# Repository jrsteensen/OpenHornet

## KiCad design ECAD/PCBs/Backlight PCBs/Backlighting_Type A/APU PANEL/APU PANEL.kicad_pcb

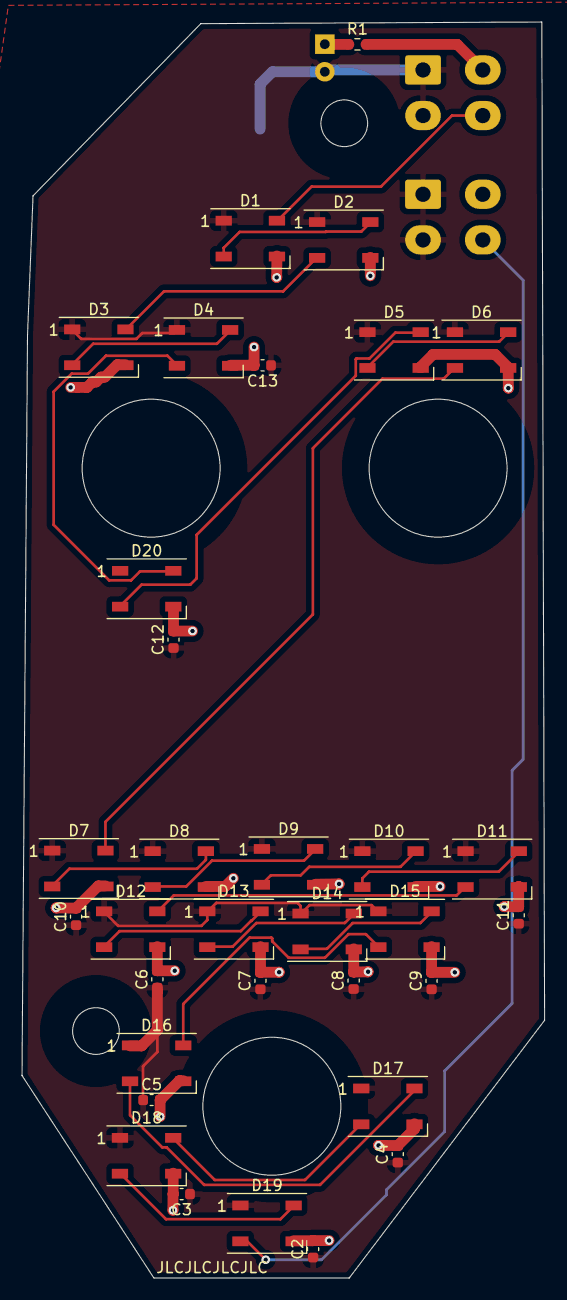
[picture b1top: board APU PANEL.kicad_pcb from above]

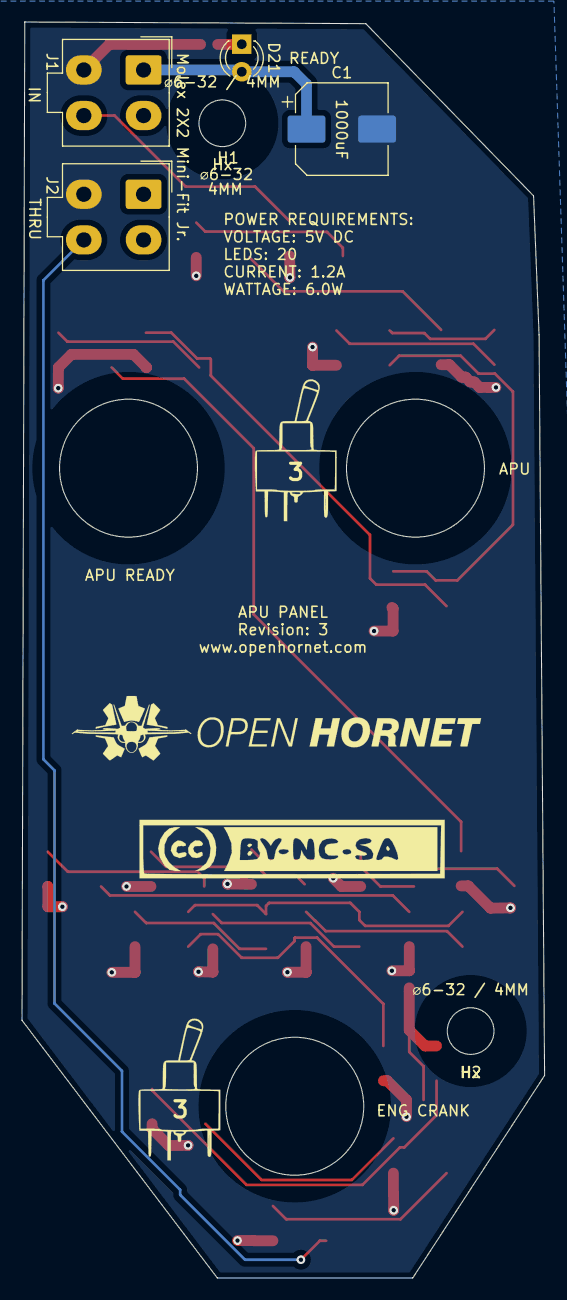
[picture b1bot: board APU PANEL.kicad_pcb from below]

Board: 2 copper layers, 48.1 x 115.6 mm, 41 parts (4 on the bottom side), 24 nets.

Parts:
2, 3: 631H_Toggle_13mm_x_13mm
4, 5: OH_Panel_Fastner_Keepout; OH_Panel_6-32_PHS
C1: 1000uF (C_Polarized); CP_Elec_8x10
C2, C3, C4, C5, C6, C7, C8, C9, C10, C11, C12, C13: 0.1uF; C_0603_1608Metric
D1, D2, D3, D4, D5, D6, D7, D8, D9, D10, D11, D12, D13, D14, D15, D16, D17, D18, D19, D20: WS2812B; LED_WS2812B_PLCC4_5.0x5.0mm_P3.2mm
D21: LED; LED_D3.0mm
J1, J2: 2x02; Molex_Mini-Fit_Jr_5566-04A_2x02_P4.20mm_Vertical
R1: 470; R_0603_1608Metric

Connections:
/DATAIN: D1.4 (DIN), J1.4
/DATAOUT: D19.2 (DOUT), J2.4
/LED+5V: C1.1, C2.1, C3.1, C4.1, C5.1, C6.1, C7.1, C8.1, C9.1, C10.1, C11.1, C12.1, C13.1, D1.1 (VDD), D2.1 (VDD), D3.1 (VDD), D4.1 (VDD), D5.1 (VDD), D6.1 (VDD), D7.1 (VDD), D8.1 (VDD), D9.1 (VDD), D10.1 (VDD), D11.1 (VDD), D12.1 (VDD), D13.1 (VDD), D14.1 (VDD), D15.1 (VDD), D16.1 (VDD), D17.1 (VDD), D18.1 (VDD), D19.1 (VDD), D20.1 (VDD), D21.2 (A), J1.1, J1.2, J2.1, J2.2
/LEDGND: C1.2, C2.2, C3.2, C4.2, C5.2, C6.2, C7.2, C8.2, C9.2, C10.2, C11.2, C12.2, C13.2, D1.3 (VSS), D2.3 (VSS), D3.3 (VSS), D4.3 (VSS), D5.3 (VSS), D6.3 (VSS), D7.3 (VSS), D8.3 (VSS), D9.3 (VSS), D10.3 (VSS), D11.3 (VSS), D12.3 (VSS), D13.3 (VSS), D14.3 (VSS), D15.3 (VSS), D16.3 (VSS), D17.3 (VSS), D18.3 (VSS), D19.3 (VSS), D20.3 (VSS), J1.3, J2.3, R1.2
unnamed: D1.2 (DOUT), D2.4 (DIN)
unnamed: D2.2 (DOUT), D3.4 (DIN)
unnamed: D3.2 (DOUT), D4.4 (DIN)
unnamed: D5.2 (DOUT), D6.4 (DIN)
unnamed: D6.2 (DOUT), D7.4 (DIN)
unnamed: D7.2 (DOUT), D8.4 (DIN)
unnamed: D8.2 (DOUT), D9.4 (DIN)
unnamed: D10.2 (DOUT), D11.4 (DIN)
unnamed: D9.2 (DOUT), D10.4 (DIN)
unnamed: D11.2 (DOUT), D12.4 (DIN)
unnamed: D12.2 (DOUT), D13.4 (DIN)
unnamed: D13.2 (DOUT), D14.4 (DIN)
unnamed: D14.2 (DOUT), D15.4 (DIN)
unnamed: D15.2 (DOUT), D16.4 (DIN)
unnamed: D16.2 (DOUT), D17.4 (DIN)
unnamed: D17.2 (DOUT), D18.4 (DIN)
unnamed: D18.2 (DOUT), D19.4 (DIN)
unnamed: D5.4 (DIN), D20.2 (DOUT)
unnamed: D4.2 (DOUT), D20.4 (DIN)
unnamed: D21.1 (K), R1.1

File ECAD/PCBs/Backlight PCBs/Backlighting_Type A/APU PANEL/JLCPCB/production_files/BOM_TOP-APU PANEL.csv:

Comment,Designator,Footprint,LCSC
0.1uF,"C10,C11,C12,C13,C2,C3,C4,C5,C6,C7,C8,C9",C_0603_1608Metric,C14663
470,R1,R_0603_1608Metric,C23179
WS2812B,"D1,D10,D11,D12,D13,D14,D15,D16,D17,D18,D19,D2,D20,D3,D4,D5,D6,D7,D8,D9",LED_WS2812B_PLCC4_5.0x5.0mm_P3.2mm,C2761795

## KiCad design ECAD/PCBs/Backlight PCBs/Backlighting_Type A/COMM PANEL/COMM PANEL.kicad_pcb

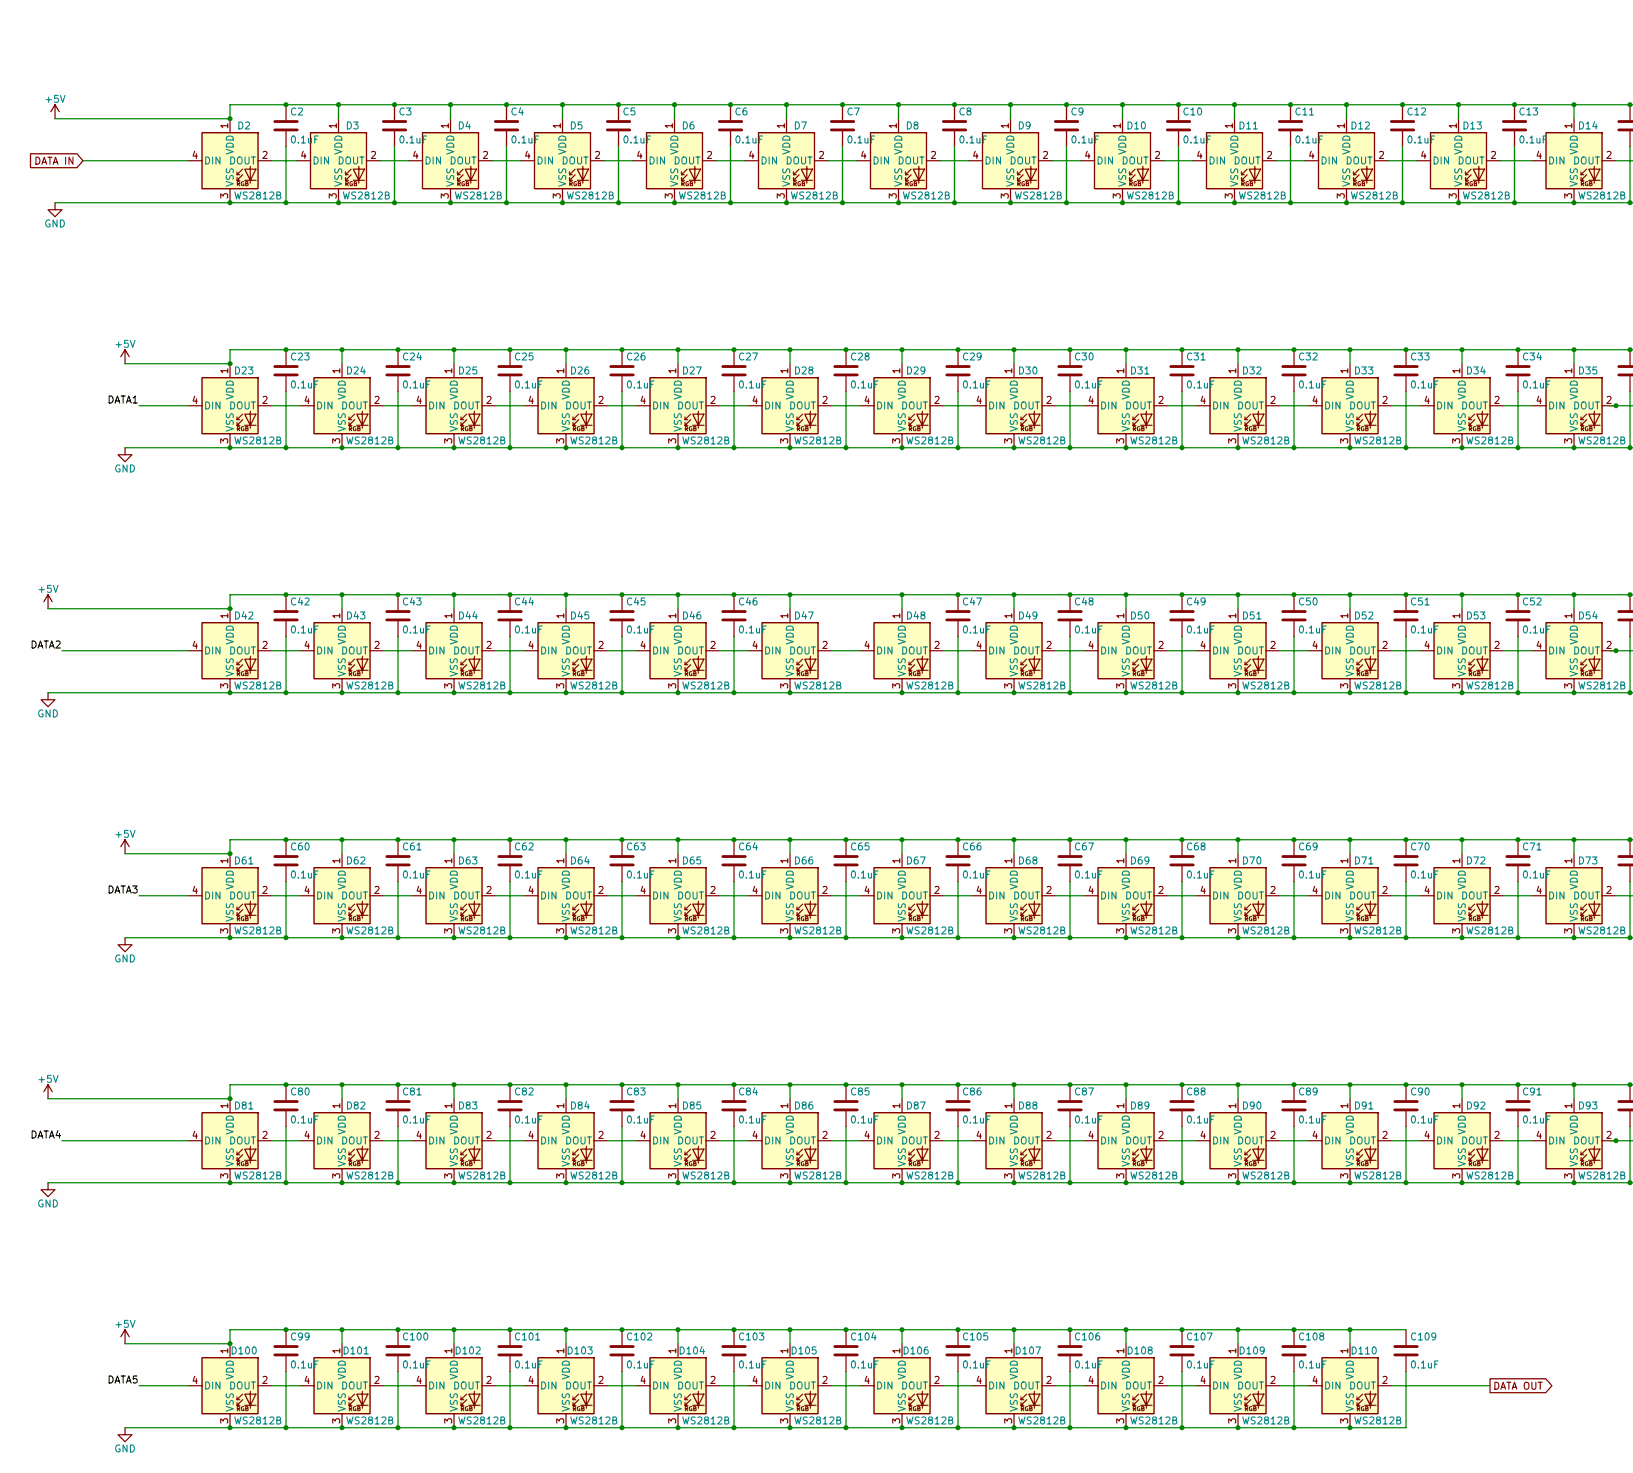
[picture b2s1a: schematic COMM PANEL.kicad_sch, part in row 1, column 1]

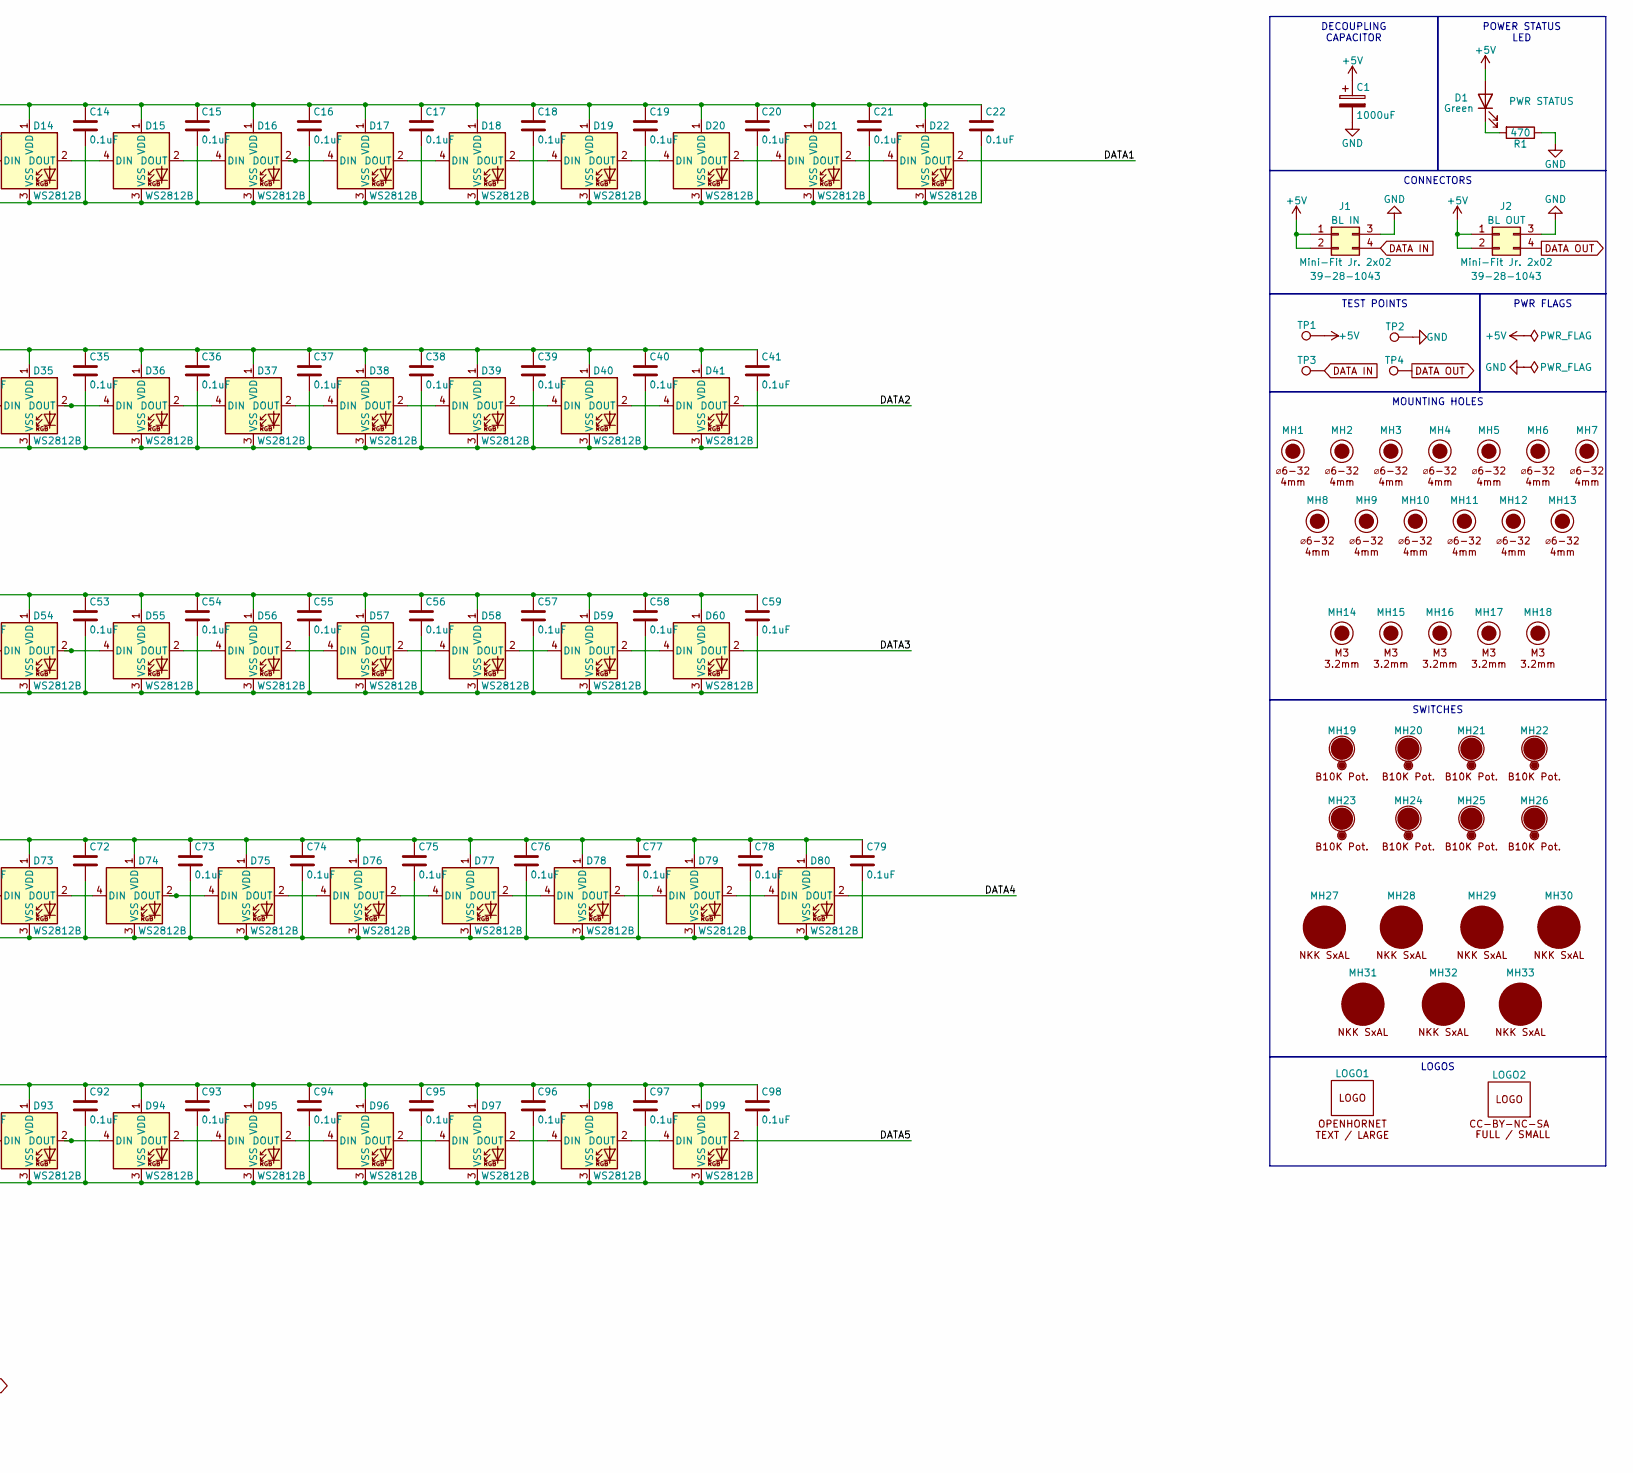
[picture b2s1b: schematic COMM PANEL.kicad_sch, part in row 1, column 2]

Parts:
C1: 1000uF; CP_Elec_8x10; Manufacturer PN UWT0J102MNL1GS; LCSC C445083
C2, C3, C4, C5, C6, C7, C8, C9, C10, C11, C12, C13, C14, C15, C16, C17, C18, C19, C20, C21, C22, C23, C24, C25, C26, C27, C28, C29, C30, C31, C32, C33, C34, C35, C36, C37, C38, C39, C40, C41, C42, C43, C44, C45, C46, C47, C48, C49, C50, C51, C52, C53, C54, C55, C56, C57, C58, C59, C60, C61, C62, C63, C64, C65, C66, C67, C68, C69, C70, C71, C72, C73, C74, C75, C76, C77, C78, C79, C80, C81, C82, C83, C84, C85, C86, C87, C88, C89, C90, C91, C92, C93, C94, C95, C96, C97, C98, C99, C100, C101, C102, C103, C104, C105, C106, C107, C108, C109: 0.1uF; C_0603_1608Metric; Manufacturer PN CC0603KRX7R9BB104; LCSC C14663
D1: Green; LED_D3.0mm
D2, D3, D4, D5, D6, D7, D8, D9, D10, D11, D12, D13, D14, D15, D16, D17, D18, D19, D20, D21, D22, D23, D24, D25, D26, D27, D28, D29, D30, D31, D32, D33, D34, D35, D36, D37, D38, D39, D40, D41, D42, D43, D44, D45, D46, D47, D48, D49, D50, D51, D52, D53, D54, D55, D56, D57, D58, D59, D60, D61, D62, D63, D64, D65, D66, D67, D68, D69, D70, D71, D72, D73, D74, D75, D76, D77, D78, D79, D80, D81, D82, D83, D84, D85, D86, D87, D88, D89, D90, D91, D92, D93, D94, D95, D96, D97, D98, D99, D100, D101, D102, D103, D104, D105, D106, D107, D108, D109, D110: WS2812B; LED_WS2812B_PLCC4_5.0x5.0mm_P3.2mm; Manufacturer PN WS2812B; LCSC C2761795
J1, J2: Mini-Fit Jr. 2x02; Molex_Mini-Fit_Jr_5566-04A_2x02_P4.20mm_Vertical; Manufacturer PN 39-28-1043; LCSC C293502
LOGO1: LOGO; LOGO_OH_Text_Large
LOGO2: LOGO; LOGO_CC-BY-NC-SA_Full_Small
MH1, MH2, MH3, MH4, MH5, MH6, MH7, MH8, MH9, MH10, MH11, MH12, MH13: 6x32 / 4mm; MountingHole_6-32_PHS
MH14, MH15, MH16, MH17, MH18: M3 / 3.2mm; MountingHole_3.2mm_M3_DIN965
MH19, MH20, MH21, MH22, MH23, MH24, MH25, MH26: Pot_B10K; BR10K_Pot_11mm_x_11mm; Manufacturer PN P0915N-FC20BR10K
MH27, MH28, MH29, MH30, MH31, MH32, MH33: Switch_NKK SxAL; SxAL_Toggle_13x13mm; Manufacturer PN SxAL
R1: 470; R_0603_1608Metric; Manufacturer PN 0603WAF4700T5E; LCSC C23179
TP1, TP2, TP3, TP4: TestPoint; TestPoint_THTPad_D1.5mm_Drill0.7mm

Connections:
+5V: C1.1, C2.1, C3.1, C4.1, C5.1, C6.1, C7.1, C8.1, C9.1, C10.1, C11.1, C12.1, C13.1, C14.1, C15.1, C16.1, C17.1, C18.1, C19.1, C20.1, C21.1, C22.1, C23.1, C24.1, C25.1, C26.1, C27.1, C28.1, C29.1, C30.1, C31.1, C32.1, C33.1, C34.1, C35.1, C36.1, C37.1, C38.1, C39.1, C40.1, C41.1, C42.1, C43.1, C44.1, C45.1, C46.1, C47.1, C48.1, C49.1, C50.1, C51.1, C52.1, C53.1, C54.1, C55.1, C56.1, C57.1, C58.1, C59.1, C60.1, C61.1, C62.1, C63.1, C64.1, C65.1, C66.1, C67.1, C68.1, C69.1, C70.1, C71.1, C72.1, C73.1, C74.1, C75.1, C76.1, C77.1, C78.1, C79.1, C80.1, C81.1, C82.1, C83.1, C84.1, C85.1, C86.1, C87.1, C88.1, C89.1, C90.1, C91.1, C92.1, C93.1, C94.1, C95.1, C96.1, C97.1, C98.1, C99.1, C100.1, C101.1, C102.1, C103.1, C104.1, C105.1, C106.1, C107.1, C108.1, C109.1, D1.2 (A), D2.1 (VDD), D3.1 (VDD), D4.1 (VDD), D5.1 (VDD), D6.1 (VDD), D7.1 (VDD), D8.1 (VDD), D9.1 (VDD), D10.1 (VDD), D11.1 (VDD), D12.1 (VDD), D13.1 (VDD), D14.1 (VDD), D15.1 (VDD), D16.1 (VDD), D17.1 (VDD), D18.1 (VDD), D19.1 (VDD), D20.1 (VDD), D21.1 (VDD), D22.1 (VDD), D23.1 (VDD), D24.1 (VDD), D25.1 (VDD), D26.1 (VDD), D27.1 (VDD), D28.1 (VDD), D29.1 (VDD), D30.1 (VDD), D31.1 (VDD), D32.1 (VDD), D33.1 (VDD), D34.1 (VDD), D35.1 (VDD), D36.1 (VDD), D37.1 (VDD), D38.1 (VDD), D39.1 (VDD), D40.1 (VDD), D41.1 (VDD), D42.1 (VDD), D43.1 (VDD), D44.1 (VDD), D45.1 (VDD), D46.1 (VDD), D47.1 (VDD), D48.1 (VDD), D49.1 (VDD), D50.1 (VDD), D51.1 (VDD), D52.1 (VDD), D53.1 (VDD), D54.1 (VDD), D55.1 (VDD), D56.1 (VDD), D57.1 (VDD), D58.1 (VDD), D59.1 (VDD), D60.1 (VDD), D61.1 (VDD), D62.1 (VDD), D63.1 (VDD), D64.1 (VDD), D65.1 (VDD), D66.1 (VDD), D67.1 (VDD), D68.1 (VDD), D69.1 (VDD), D70.1 (VDD), D71.1 (VDD), D72.1 (VDD), D73.1 (VDD), D74.1 (VDD), D75.1 (VDD), D76.1 (VDD), D77.1 (VDD), D78.1 (VDD), D79.1 (VDD), D80.1 (VDD), D81.1 (VDD), D82.1 (VDD), D83.1 (VDD), D84.1 (VDD), D85.1 (VDD), D86.1 (VDD), D87.1 (VDD), D88.1 (VDD), D89.1 (VDD), D90.1 (VDD), D91.1 (VDD), D92.1 (VDD), D93.1 (VDD), D94.1 (VDD), D95.1 (VDD), D96.1 (VDD), D97.1 (VDD), D98.1 (VDD), D99.1 (VDD), D100.1 (VDD), D101.1 (VDD), D102.1 (VDD), D103.1 (VDD), D104.1 (VDD), D105.1 (VDD), D106.1 (VDD), D107.1 (VDD), D108.1 (VDD), D109.1 (VDD), D110.1 (VDD), J1.1, J1.2 (Pin_3), J2.1, J2.2 (Pin_3), TP1.1
/DATA1: D22.2 (DOUT), D23.4 (DIN)
/DATA2: D41.2 (DOUT), D42.4 (DIN)
/DATA3: D60.2 (DOUT), D61.4 (DIN)
/DATA4: D80.2 (DOUT), D81.4 (DIN)
/DATA5: D99.2 (DOUT), D100.4 (DIN)
DATA IN: D2.4 (DIN), J1.4, TP3.1
DATA OUT: D110.2 (DOUT), J2.4, TP4.1
GND: C1.2, C2.2, C3.2, C4.2, C5.2, C6.2, C7.2, C8.2, C9.2, C10.2, C11.2, C12.2, C13.2, C14.2, C15.2, C16.2, C17.2, C18.2, C19.2, C20.2, C21.2, C22.2, C23.2, C24.2, C25.2, C26.2, C27.2, C28.2, C29.2, C30.2, C31.2, C32.2, C33.2, C34.2, C35.2, C36.2, C37.2, C38.2, C39.2, C40.2, C41.2, C42.2, C43.2, C44.2, C45.2, C46.2, C47.2, C48.2, C49.2, C50.2, C51.2, C52.2, C53.2, C54.2, C55.2, C56.2, C57.2, C58.2, C59.2, C60.2, C61.2, C62.2, C63.2, C64.2, C65.2, C66.2, C67.2, C68.2, C69.2, C70.2, C71.2, C72.2, C73.2, C74.2, C75.2, C76.2, C77.2, C78.2, C79.2, C80.2, C81.2, C82.2, C83.2, C84.2, C85.2, C86.2, C87.2, C88.2, C89.2, C90.2, C91.2, C92.2, C93.2, C94.2, C95.2, C96.2, C97.2, C98.2, C99.2, C100.2, C101.2, C102.2, C103.2, C104.2, C105.2, C106.2, C107.2, C108.2, C109.2, D2.3 (VSS), D3.3 (VSS), D4.3 (VSS), D5.3 (VSS), D6.3 (VSS), D7.3 (VSS), D8.3 (VSS), D9.3 (VSS), D10.3 (VSS), D11.3 (VSS), D12.3 (VSS), D13.3 (VSS), D14.3 (VSS), D15.3 (VSS), D16.3 (VSS), D17.3 (VSS), D18.3 (VSS), D19.3 (VSS), D20.3 (VSS), D21.3 (VSS), D22.3 (VSS), D23.3 (VSS), D24.3 (VSS), D25.3 (VSS), D26.3 (VSS), D27.3 (VSS), D28.3 (VSS), D29.3 (VSS), D30.3 (VSS), D31.3 (VSS), D32.3 (VSS), D33.3 (VSS), D34.3 (VSS), D35.3 (VSS), D36.3 (VSS), D37.3 (VSS), D38.3 (VSS), D39.3 (VSS), D40.3 (VSS), D41.3 (VSS), D42.3 (VSS), D43.3 (VSS), D44.3 (VSS), D45.3 (VSS), D46.3 (VSS), D47.3 (VSS), D48.3 (VSS), D49.3 (VSS), D50.3 (VSS), D51.3 (VSS), D52.3 (VSS), D53.3 (VSS), D54.3 (VSS), D55.3 (VSS), D56.3 (VSS), D57.3 (VSS), D58.3 (VSS), D59.3 (VSS), D60.3 (VSS), D61.3 (VSS), D62.3 (VSS), D63.3 (VSS), D64.3 (VSS), D65.3 (VSS), D66.3 (VSS), D67.3 (VSS), D68.3 (VSS), D69.3 (VSS), D70.3 (VSS), D71.3 (VSS), D72.3 (VSS), D73.3 (VSS), D74.3 (VSS), D75.3 (VSS), D76.3 (VSS), D77.3 (VSS), D78.3 (VSS), D79.3 (VSS), D80.3 (VSS), D81.3 (VSS), D82.3 (VSS), D83.3 (VSS), D84.3 (VSS), D85.3 (VSS), D86.3 (VSS), D87.3 (VSS), D88.3 (VSS), D89.3 (VSS), D90.3 (VSS), D91.3 (VSS), D92.3 (VSS), D93.3 (VSS), D94.3 (VSS), D95.3 (VSS), D96.3 (VSS), D97.3 (VSS), D98.3 (VSS), D99.3 (VSS), D100.3 (VSS), D101.3 (VSS), D102.3 (VSS), D103.3 (VSS), D104.3 (VSS), D105.3 (VSS), D106.3 (VSS), D107.3 (VSS), D108.3 (VSS), D109.3 (VSS), D110.3 (VSS), J1.3 (Pin_2), J2.3 (Pin_2), R1.1, TP2.1
unnamed: D1.1 (K), R1.2
unnamed: D2.2 (DOUT), D3.4 (DIN)
unnamed: D3.2 (DOUT), D4.4 (DIN)
unnamed: D4.2 (DOUT), D5.4 (DIN)
unnamed: D5.2 (DOUT), D6.4 (DIN)
unnamed: D6.2 (DOUT), D7.4 (DIN)
unnamed: D7.2 (DOUT), D8.4 (DIN)
unnamed: D8.2 (DOUT), D9.4 (DIN)
unnamed: D9.2 (DOUT), D10.4 (DIN)
unnamed: D10.2 (DOUT), D11.4 (DIN)
unnamed: D11.2 (DOUT), D12.4 (DIN)
unnamed: D12.2 (DOUT), D13.4 (DIN)
unnamed: D13.2 (DOUT), D14.4 (DIN)
unnamed: D14.2 (DOUT), D15.4 (DIN)
unnamed: D15.2 (DOUT), D16.4 (DIN)
unnamed: D16.2 (DOUT), D17.4 (DIN)
unnamed: D17.2 (DOUT), D18.4 (DIN)
unnamed: D18.2 (DOUT), D19.4 (DIN)
unnamed: D19.2 (DOUT), D20.4 (DIN)
unnamed: D20.2 (DOUT), D21.4 (DIN)
unnamed: D21.2 (DOUT), D22.4 (DIN)
unnamed: D23.2 (DOUT), D24.4 (DIN)
unnamed: D24.2 (DOUT), D25.4 (DIN)
unnamed: D25.2 (DOUT), D26.4 (DIN)
unnamed: D26.2 (DOUT), D27.4 (DIN)
unnamed: D27.2 (DOUT), D28.4 (DIN)
unnamed: D28.2 (DOUT), D29.4 (DIN)
unnamed: D29.2 (DOUT), D30.4 (DIN)
unnamed: D30.2 (DOUT), D31.4 (DIN)
unnamed: D31.2 (DOUT), D32.4 (DIN)
unnamed: D32.2 (DOUT), D33.4 (DIN)
unnamed: D33.2 (DOUT), D34.4 (DIN)
unnamed: D34.2 (DOUT), D35.4 (DIN)
unnamed: D35.2 (DOUT), D36.4 (DIN)
unnamed: D36.2 (DOUT), D37.4 (DIN)
unnamed: D37.2 (DOUT), D38.4 (DIN)
unnamed: D38.2 (DOUT), D39.4 (DIN)
unnamed: D39.2 (DOUT), D40.4 (DIN)
unnamed: D40.2 (DOUT), D41.4 (DIN)
unnamed: D42.2 (DOUT), D43.4 (DIN)
unnamed: D43.2 (DOUT), D44.4 (DIN)
unnamed: D44.2 (DOUT), D45.4 (DIN)
unnamed: D45.2 (DOUT), D46.4 (DIN)
unnamed: D46.2 (DOUT), D47.4 (DIN)
unnamed: D47.2 (DOUT), D48.4 (DIN)
unnamed: D48.2 (DOUT), D49.4 (DIN)
unnamed: D49.2 (DOUT), D50.4 (DIN)
unnamed: D50.2 (DOUT), D51.4 (DIN)
unnamed: D51.2 (DOUT), D52.4 (DIN)
unnamed: D52.2 (DOUT), D53.4 (DIN)
unnamed: D53.2 (DOUT), D54.4 (DIN)
unnamed: D54.2 (DOUT), D55.4 (DIN)
unnamed: D55.2 (DOUT), D56.4 (DIN)
unnamed: D56.2 (DOUT), D57.4 (DIN)
unnamed: D57.2 (DOUT), D58.4 (DIN)
unnamed: D58.2 (DOUT), D59.4 (DIN)
unnamed: D59.2 (DOUT), D60.4 (DIN)
unnamed: D61.2 (DOUT), D62.4 (DIN)
unnamed: D62.2 (DOUT), D63.4 (DIN)
unnamed: D63.2 (DOUT), D64.4 (DIN)
unnamed: D64.2 (DOUT), D65.4 (DIN)
unnamed: D65.2 (DOUT), D66.4 (DIN)
unnamed: D66.2 (DOUT), D67.4 (DIN)
unnamed: D67.2 (DOUT), D68.4 (DIN)
unnamed: D68.2 (DOUT), D69.4 (DIN)
unnamed: D69.2 (DOUT), D70.4 (DIN)
unnamed: D70.2 (DOUT), D71.4 (DIN)
unnamed: D71.2 (DOUT), D72.4 (DIN)
unnamed: D72.2 (DOUT), D73.4 (DIN)
unnamed: D73.2 (DOUT), D74.4 (DIN)
unnamed: D74.2 (DOUT), D75.4 (DIN)
unnamed: D75.2 (DOUT), D76.4 (DIN)
unnamed: D76.2 (DOUT), D77.4 (DIN)
unnamed: D77.2 (DOUT), D78.4 (DIN)
unnamed: D78.2 (DOUT), D79.4 (DIN)
unnamed: D79.2 (DOUT), D80.4 (DIN)
unnamed: D81.2 (DOUT), D82.4 (DIN)
unnamed: D82.2 (DOUT), D83.4 (DIN)
unnamed: D83.2 (DOUT), D84.4 (DIN)
unnamed: D84.2 (DOUT), D85.4 (DIN)
unnamed: D85.2 (DOUT), D86.4 (DIN)
unnamed: D86.2 (DOUT), D87.4 (DIN)
unnamed: D87.2 (DOUT), D88.4 (DIN)
unnamed: D88.2 (DOUT), D89.4 (DIN)
unnamed: D89.2 (DOUT), D90.4 (DIN)
unnamed: D90.2 (DOUT), D91.4 (DIN)
unnamed: D91.2 (DOUT), D92.4 (DIN)
unnamed: D92.2 (DOUT), D93.4 (DIN)
unnamed: D93.2 (DOUT), D94.4 (DIN)
unnamed: D94.2 (DOUT), D95.4 (DIN)
unnamed: D95.2 (DOUT), D96.4 (DIN)
unnamed: D96.2 (DOUT), D97.4 (DIN)
unnamed: D97.2 (DOUT), D98.4 (DIN)
unnamed: D98.2 (DOUT), D99.4 (DIN)
unnamed: D100.2 (DOUT), D101.4 (DIN)
unnamed: D101.2 (DOUT), D102.4 (DIN)
unnamed: D102.2 (DOUT), D103.4 (DIN)
unnamed: D103.2 (DOUT), D104.4 (DIN)
unnamed: D104.2 (DOUT), D105.4 (DIN)
unnamed: D105.2 (DOUT), D106.4 (DIN)
unnamed: D106.2 (DOUT), D107.4 (DIN)
unnamed: D107.2 (DOUT), D108.4 (DIN)
unnamed: D108.2 (DOUT), D109.4 (DIN)
unnamed: D109.2 (DOUT), D110.4 (DIN)

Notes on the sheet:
SWITCHES
DECOUPLING CAPACITOR
LOGOS
POWER STATUS LED
PWR FLAGS
MOUNTING HOLES
CONNECTORS
TEST POINTS

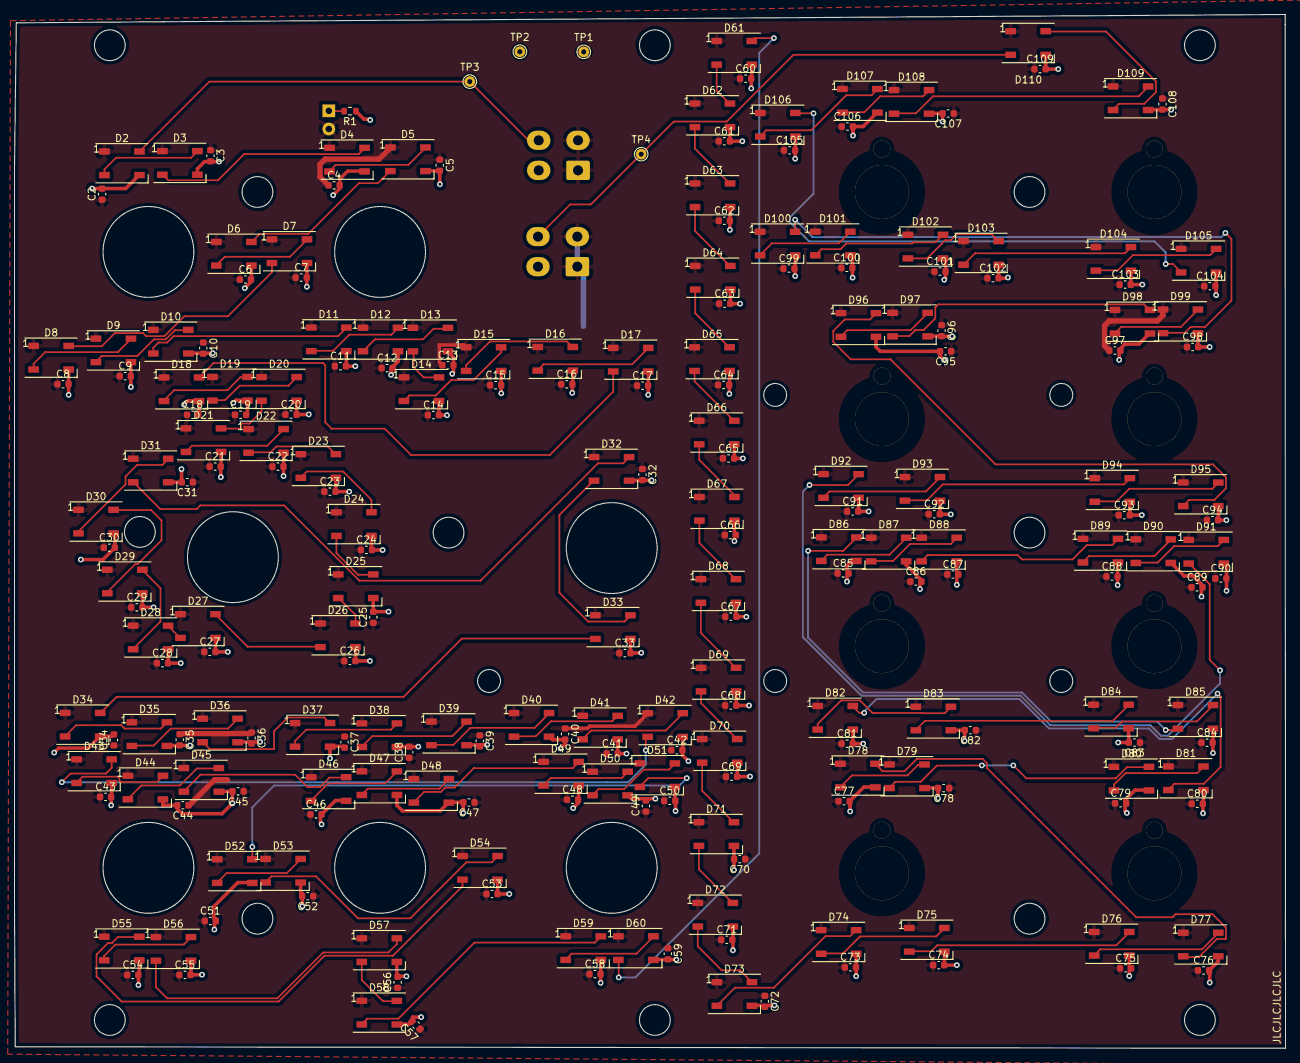
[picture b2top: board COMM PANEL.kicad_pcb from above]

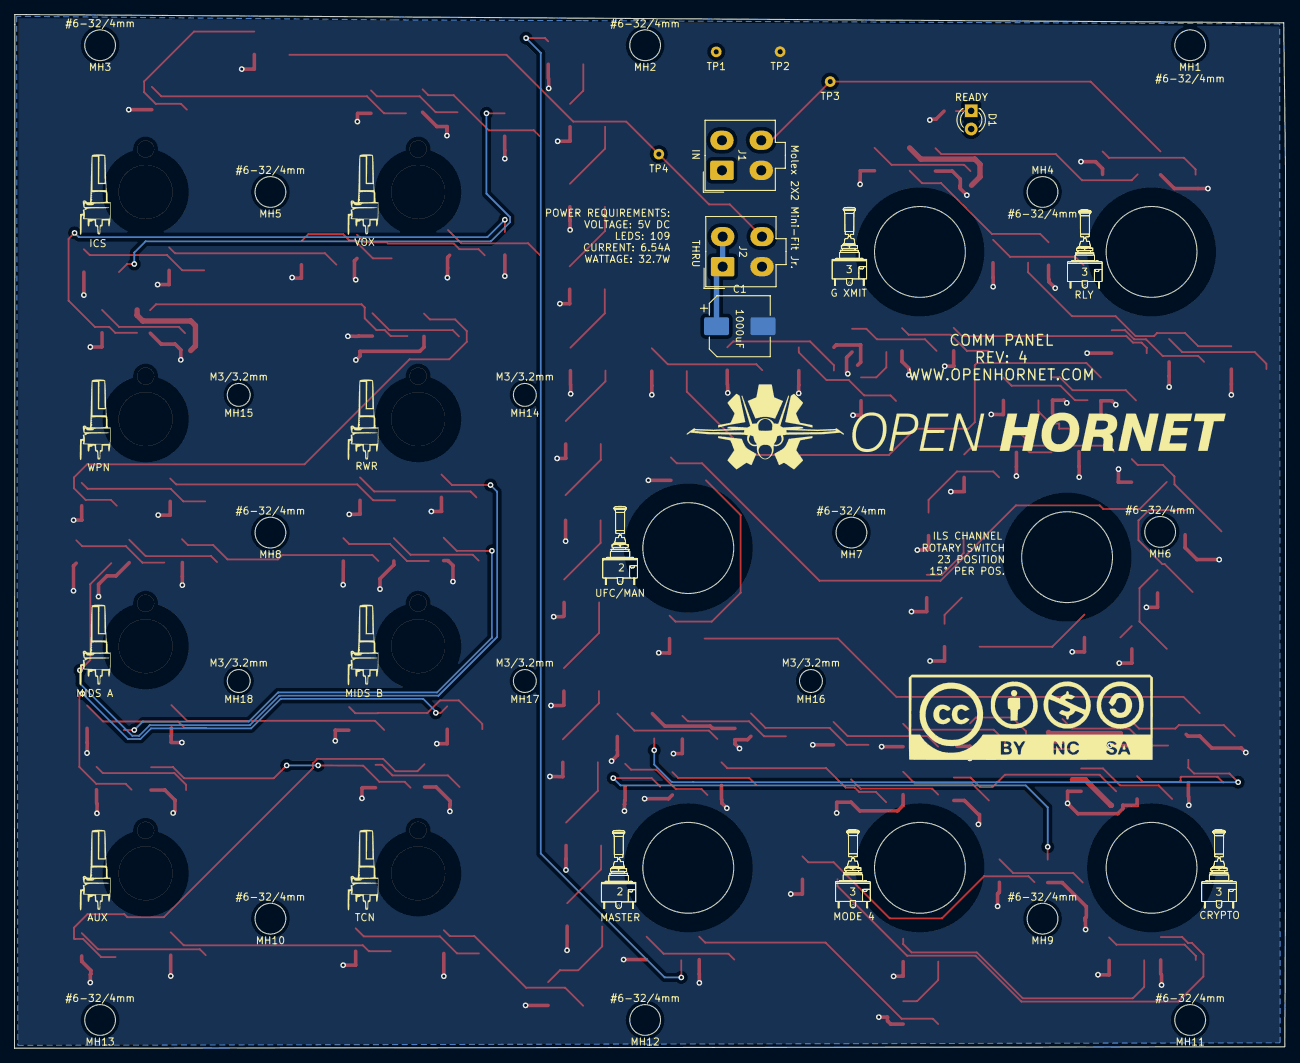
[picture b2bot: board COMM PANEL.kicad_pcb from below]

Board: 2 copper layers, 177.7 x 144.5 mm, 275 parts (38 on the bottom side), 113 nets.

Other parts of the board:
LOGO3, LOGO4, LOGO12, LOGO13: LOGO; S3AL_Toggle_Silkscreen
LOGO5, LOGO6, LOGO7, LOGO8, LOGO10, LOGO11, LOGO15, LOGO16: LOGO; BR10KPot
LOGO9, LOGO14: LOGO; S2AL_Toggle_Silkscreen

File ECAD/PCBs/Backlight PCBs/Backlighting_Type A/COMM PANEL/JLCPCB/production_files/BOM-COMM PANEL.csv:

Comment,Designator,Footprint,LCSC
0.1uF,"C10,C100,C101,C102,C103,C104,C105,C106,C107,C108,C109,C11,C12,C13,C14,C15,C16,C17,C18,C19,C2,C20,C21,C22,C23,C24,C25,C26,C27,C28,C29,C3,C30,C31,C32,C33,C34,C35,C36,C37,C38,C39,C4,C40,C41,C42,C43,C44,C45,C46,C47,C48,C49,C5,C50,C51,C52,C53,C54,C55,C56,C57,C58,C59,C6,C60,C61,C62,C63,C64,C65,C66,C67,C68,C69,C7,C70,C71,C72,C73,C74,C75,C76,C77,C78,C79,C8,C80,C81,C82,C83,C84,C85,C86,C87,C88,C89,C9,C90,C91,C92,C93,C94,C95,C96,C97,C98,C99",C_0603_1608Metric,C14663
470,R1,R_0603_1608Metric,C23179
WS2812B,"D10,D100,D101,D102,D103,D104,D105,D106,D107,D108,D109,D11,D110,D12,D13,D14,D15,D16,D17,D18,D19,D2,D20,D21,D22,D23,D24,D25,D26,D27,D28,D29,D3,D30,D31,D32,D33,D34,D35,D36,D37,D38,D39,D4,D40,D41,D42,D43,D44,D45,D46,D47,D48,D49,D5,D50,D51,D52,D53,D54,D55,D56,D57,D58,D59,D6,D60,D61,D62,D63,D64,D65,D66,D67,D68,D69,D7,D70,D71,D72,D73,D74,D75,D76,D77,D78,D79,D8,D80,D81,D82,D83,D84,D85,D86,D87,D88,D89,D9,D90,D91,D92,D93,D94,D95,D96,D97,D98,D99",LED_WS2812B_PLCC4_5.0x5.0mm_P3.2mm,C2761795
Mini-Fit Jr. 2x02,"J1,J2",Molex_Mini-Fit_Jr_5566-04A_2x02_P4.20mm_Vertical,C293502
1000uF,C1,CP_Elec_8x10,C445083
Green,D1,LED_D3.0mm,

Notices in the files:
ECAD/PCBs/Backlight PCBs/Backlighting_Type A/APU PANEL/APU PANEL.kicad_pcb:
License:  CC BY-NC-SA
parts and their libraries:
https://creativecommons.org/licenses/by-nc-sa/4.0
